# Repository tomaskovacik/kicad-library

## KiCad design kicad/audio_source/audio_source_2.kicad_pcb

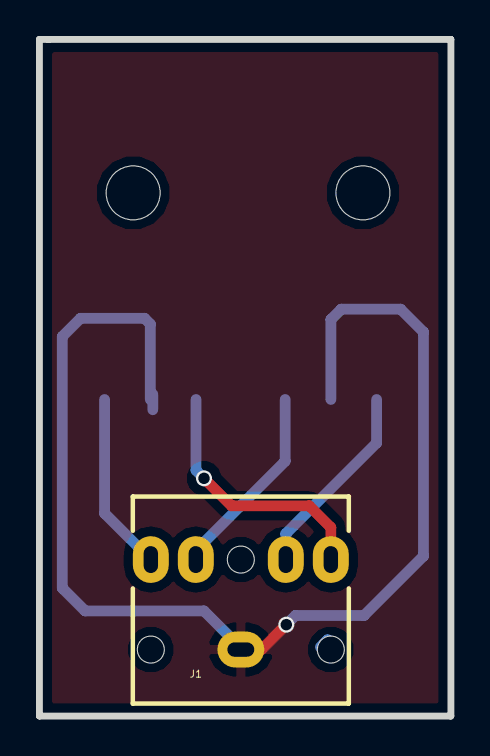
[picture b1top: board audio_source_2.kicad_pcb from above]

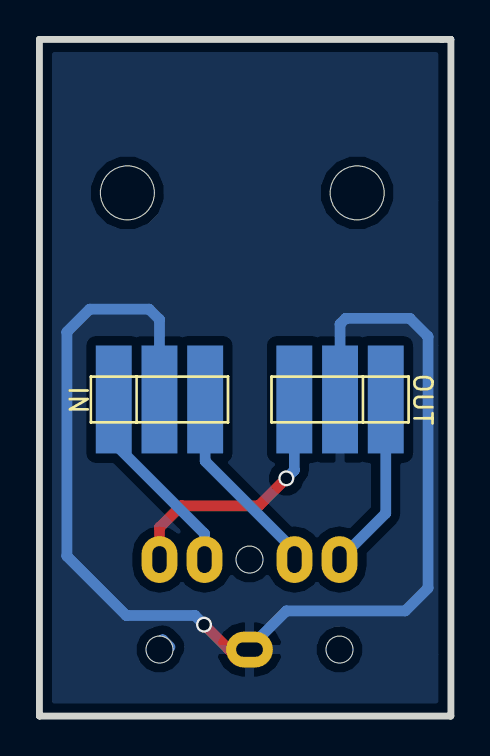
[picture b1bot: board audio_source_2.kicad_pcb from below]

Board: 2 copper layers, 22.9 x 37.6 mm, 3 parts (2 on the bottom side), 5 nets.

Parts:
J1: SCJ368R1NUS0B00G; 3.5mm_stereo_jack_PJ306M_no_screw_terminal
P1: IN; Pin_Header_Straight_1x03
P2: OUT; Pin_Header_Straight_1x03

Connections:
AGND: J1.1, P1.2, P2.2
CD_left_in: J1.4, P1.1
CD_right_in: J1.3, P1.3
RADIO_left_out: J1.5, P2.3
RADIO_right_out: J1.2, P2.1

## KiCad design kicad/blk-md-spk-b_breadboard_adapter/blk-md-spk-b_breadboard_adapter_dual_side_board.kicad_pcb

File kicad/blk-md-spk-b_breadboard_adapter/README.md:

simple breadboard adapter for cheap BLK-MD-SPK-B module from ebay based on OVC3860 with 3.5mm jack adapter

video: https://www.youtube.com/watch?v=mN-LFUUrpa8

blog: http://kovo-blog.blogspot.sk/2015/01/breadboard-adapter-for-blk-md-spk-b.html

boards are for sale, symbolic 1Euro+shipping, conntact me if you are interested, or on tindie:

schematics:
--------------

3d render:
------------

real photos:
-------------
top view,small cosmetic bug, fixed in current project on github: little rotation of jack

bottom view, with BT module soldered

adapter on breadboard

breadboard adapters for these bluetooth modules can be purchase at tindie:

BLK-MD-SPK-B https://www.tindie.com/products/tomaskovacik/breadboard-adapter-for-blk-md-spk-b/

XS3886 / S3860M-s https://www.tindie.com/products/tomaskovacik/breadboard-adapter-for-s3860m-s-sx3868/

SOYO-BT24G03 https://www.tindie.com/products/tomaskovacik/breadboard-adapter-for-soyo-bt24g03-bt-module/

F-3188 https://www.tindie.com/products/tomaskovacik/breadboard-adapter-for-f-3188-csr8645-module/

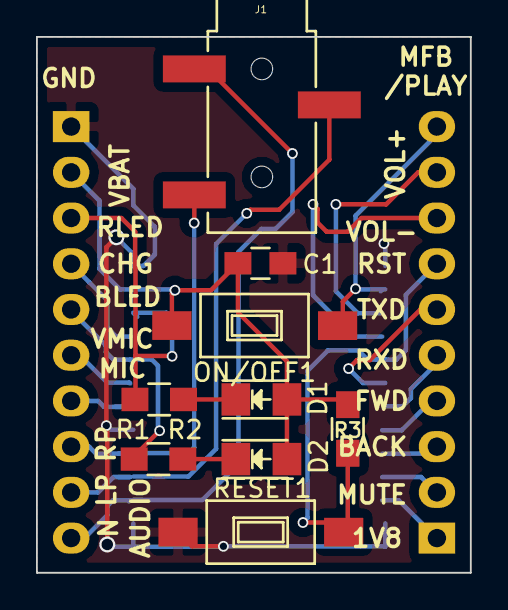
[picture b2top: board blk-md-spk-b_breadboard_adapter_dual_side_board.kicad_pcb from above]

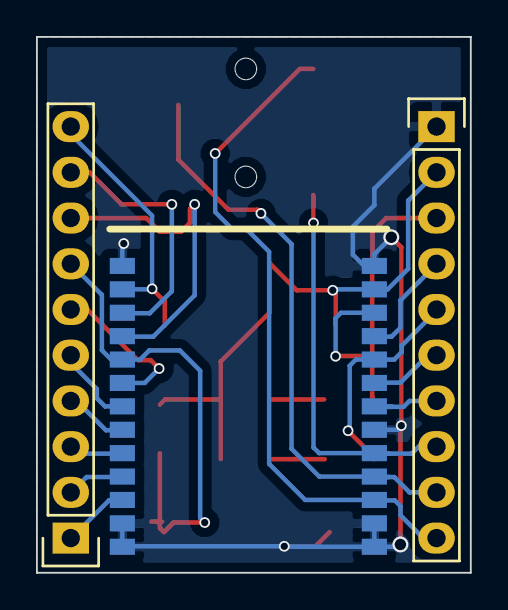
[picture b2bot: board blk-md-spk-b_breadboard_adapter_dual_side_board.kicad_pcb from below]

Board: 2 copper layers, 24.1 x 29.8 mm, 12 parts (3 on the bottom side), 22 nets.

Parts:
C1: 100n; C_0805_HandSoldering
D1, D2: LED; LED-1206
J1: SCJ368R1NUS0B00G; 3.5mm_stereo_jack_PJ320B
ON/OFF1: SW_PUSH; SW_SPST_FSMSM
P1, P2: CONNECTOR; Pin_Header_Straight_1x10
R1, R2: 470; R_0805_HandSoldering
R3: 10k; R_0805_HandSoldering
RESET1: SW_PUSH; SW_SPST_FSMSM
U1: BLK-MD-SPK-B; BLK-MD-SPK-B_no_up_silk

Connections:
GND: C1.2, P2.1, RESET1.2, U1.1, U1.2, U1.6, U1.13, U1.14, U1.25, U1.26
unnamed: C1.1, D1.2, D2.2, ON/OFF1.2, P2.2, R3.2, U1.12
unnamed: D1.1, R1.1
unnamed: D2.1, R2.1
unnamed: J1.1, P2.10, U1.3
unnamed: J1.2, P2.9, U1.4
unnamed: J1.5, P2.8, U1.5
unnamed: ON/OFF1.1, P1.10, U1.15
unnamed: P1.1, U1.24
unnamed: P1.2, U1.23
unnamed: P1.3, U1.22
unnamed: P1.4, U1.21
unnamed: P1.5, U1.20
unnamed: P1.6, U1.19
unnamed: P1.7, R3.1, RESET1.1, U1.18
unnamed: P1.8, U1.17
unnamed: P1.9, U1.16
unnamed: P2.3, R1.2, U1.11
unnamed: P2.4, U1.10
unnamed: P2.5, R2.2, U1.9
unnamed: P2.6, U1.8
unnamed: P2.7, U1.7

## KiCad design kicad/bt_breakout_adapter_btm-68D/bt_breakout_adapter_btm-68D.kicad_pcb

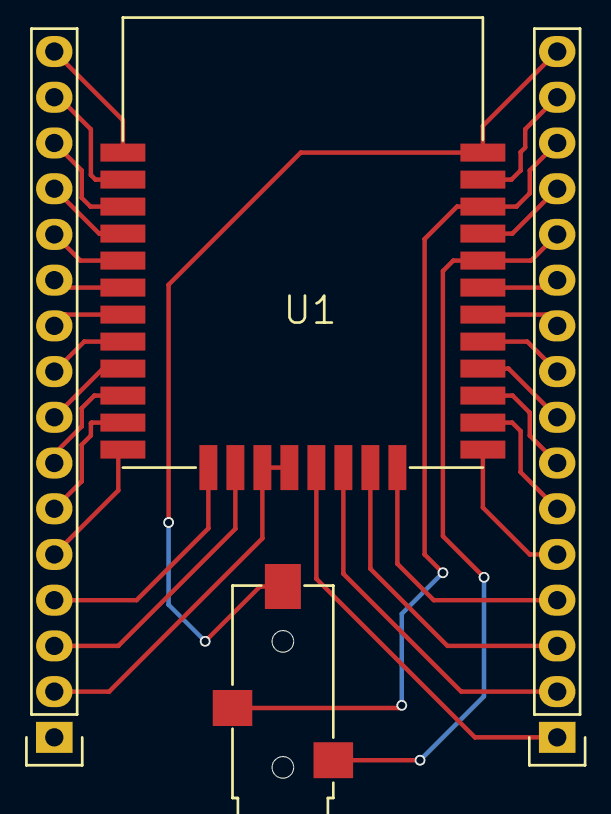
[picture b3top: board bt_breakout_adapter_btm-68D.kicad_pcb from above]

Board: 2 copper layers, 4 parts (0 on the bottom side), 31 nets.

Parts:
P1, P3: CONN_01X16; Pin_Header_Straight_1x16
P2: CONN_01X05; 3.5mm_stereo_jack_PJ3026
U1: MB-CM15113

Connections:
unnamed: P1.2, U1.15
unnamed: P1.3, U1.14
unnamed: P1.4, U1.13
unnamed: P1.5, U1.12
unnamed: P1.6, U1.11
unnamed: P1.7, U1.10
unnamed: P1.8, U1.9
unnamed: P1.9, U1.8
unnamed: P1.10, U1.7
unnamed: P1.11, U1.6
unnamed: P1.12, U1.5
unnamed: P1.13, U1.4
unnamed: P1.14, U1.3
unnamed: P1.15, U1.2
unnamed: P1.16, U1.1
unnamed: P2.1, P3.12, U1.28
unnamed: P2.2, P3.14, U1.30
unnamed: P2.5, P3.16, U1.32
unnamed: P3.1, U1.17
unnamed: P3.2, U1.18
unnamed: P3.3, U1.19
unnamed: P3.4, U1.20
unnamed: P3.5, U1.21
unnamed: P3.6, U1.22
unnamed: P3.7, U1.23
unnamed: P3.8, U1.24
unnamed: P3.9, U1.25
unnamed: P3.10, U1.26
unnamed: P3.11, U1.27
unnamed: P3.13, U1.29
unnamed: P3.15, U1.31
